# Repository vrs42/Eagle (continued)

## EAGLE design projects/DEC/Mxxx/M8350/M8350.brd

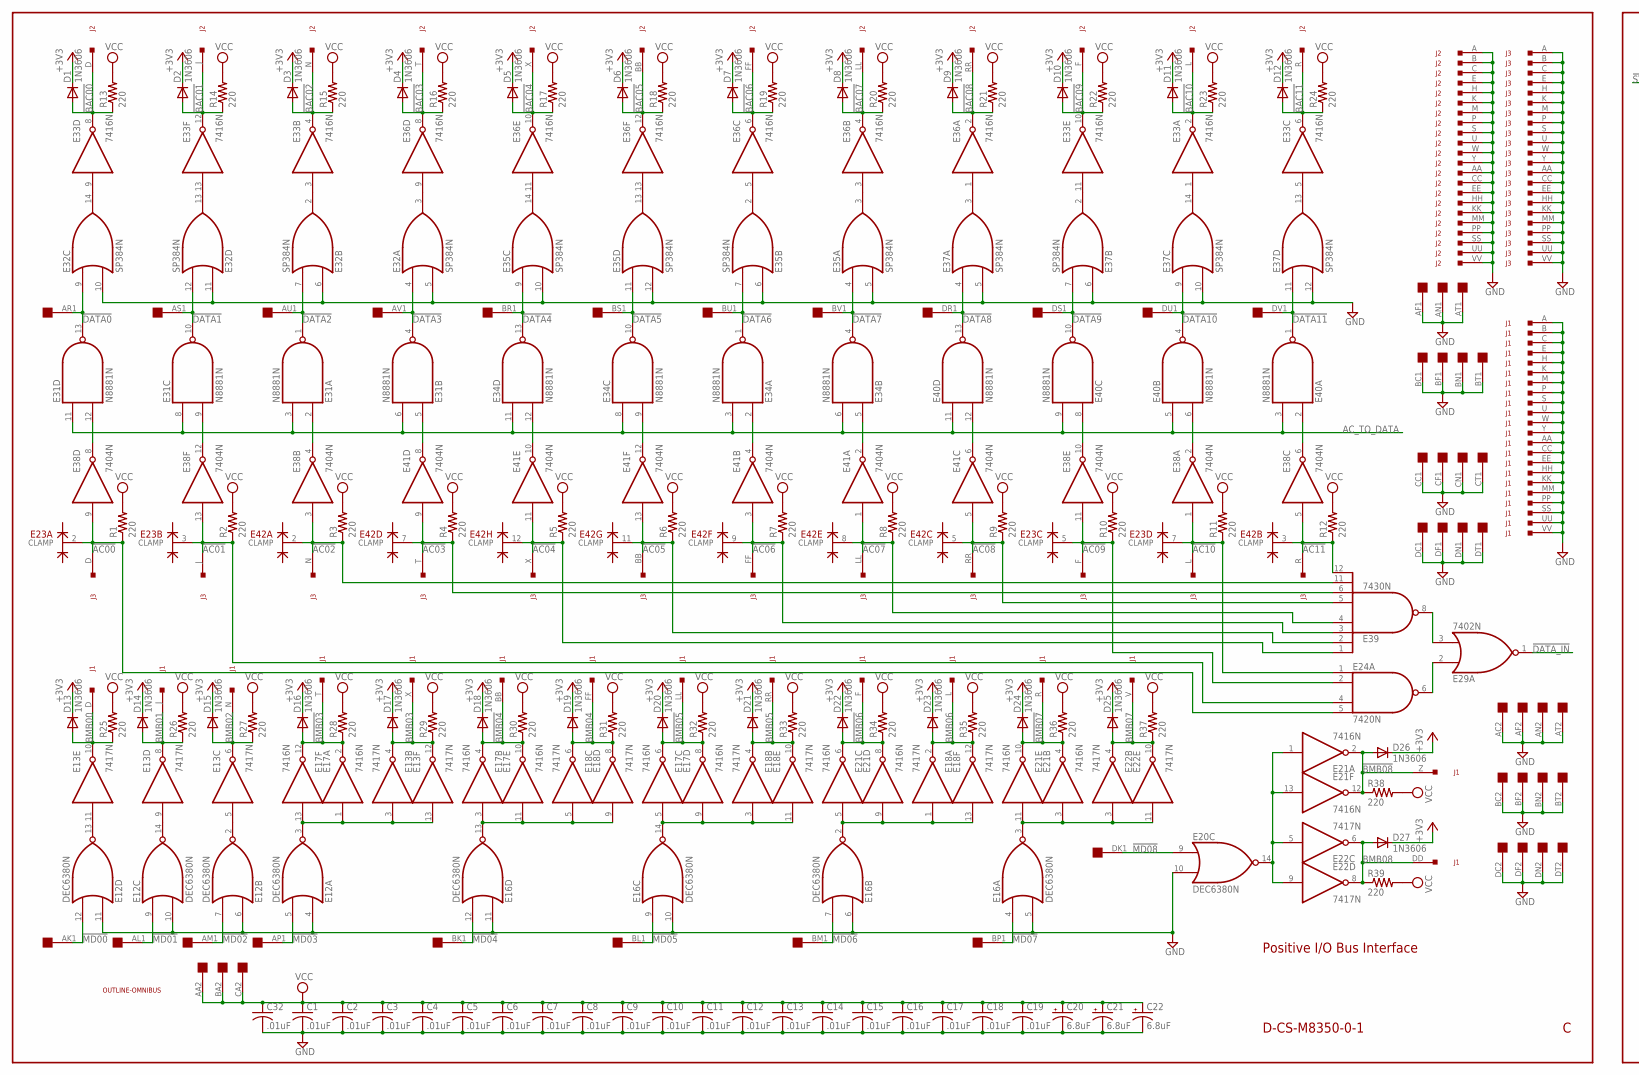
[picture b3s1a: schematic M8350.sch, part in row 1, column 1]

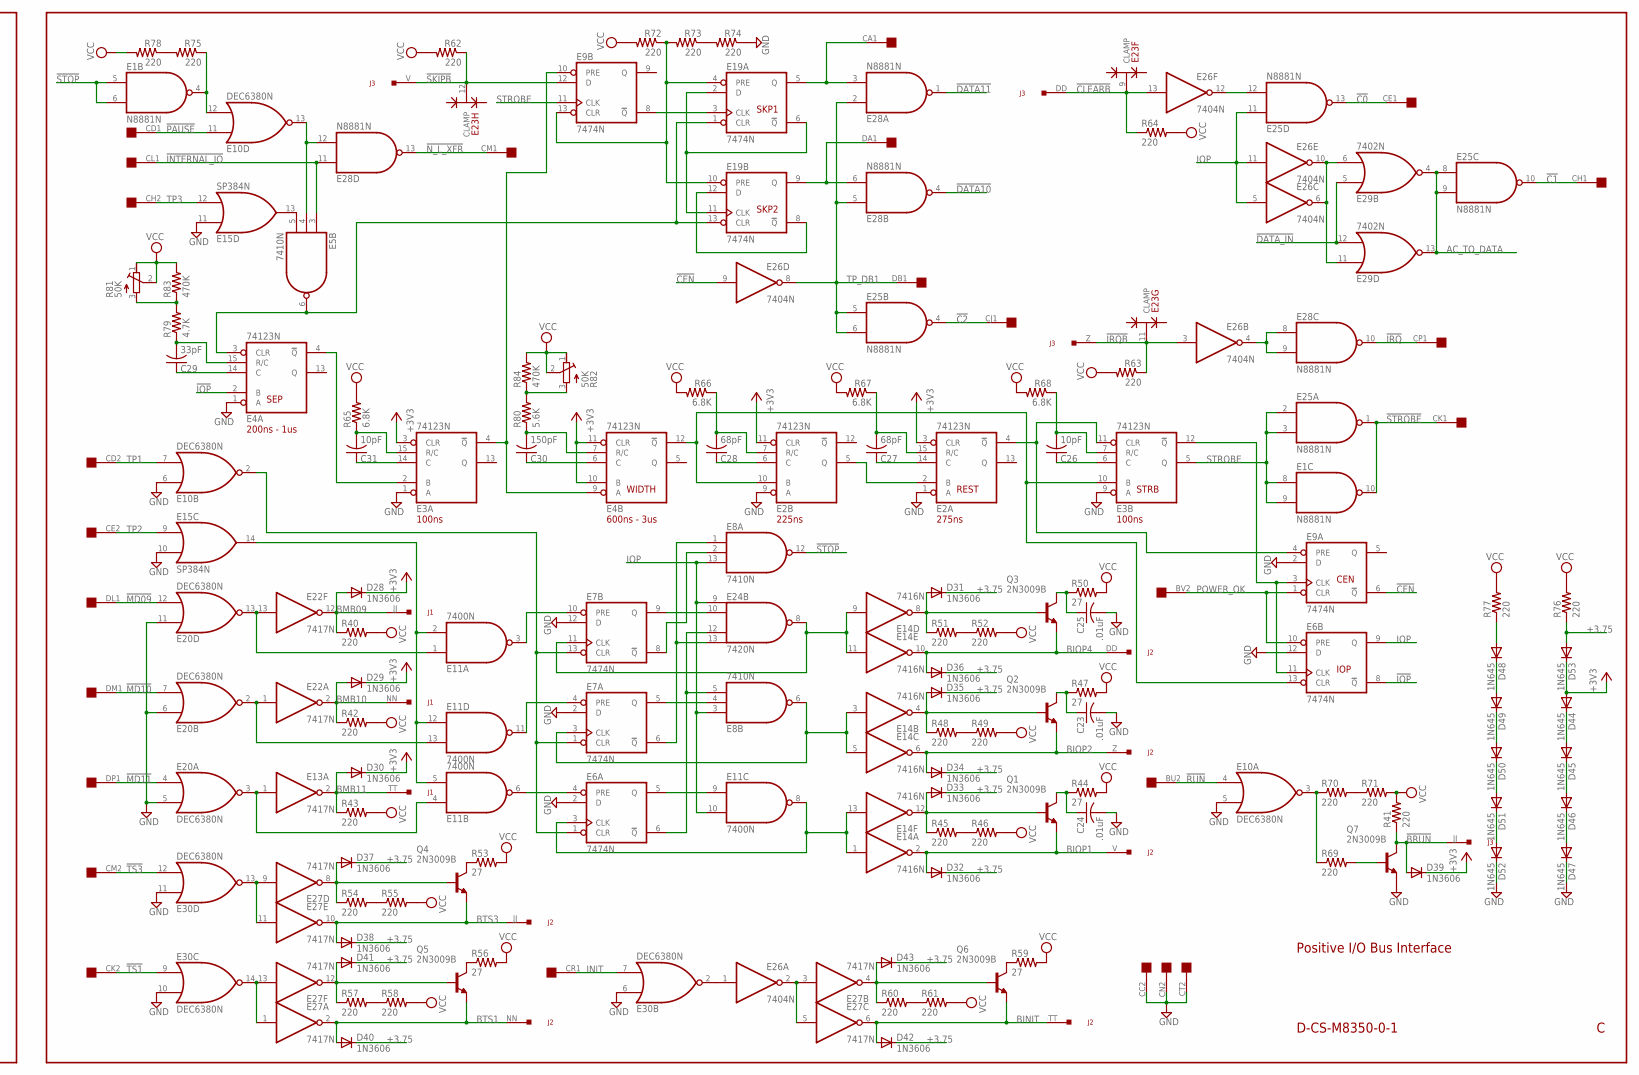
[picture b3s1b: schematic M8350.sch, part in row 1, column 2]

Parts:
C1, C2, C3, C4, C5, C6, C7, C8, C9, C10, C11, C12, C13, C14, C15, C16, C17, C18, C19, C23, C24, C25, C32: .01uF; C050-025X075
C20, C21, C22: 6.8uF; E12-8
C26, C31: 10pF; C050-025X075
C27, C28: 68pF; C050-025X075
C29: 33pF; C050-025X075
C30: 150pF; C050-025X075
D1, D2, D3, D4, D5, D6, D7, D8, D9, D10, D11, D12, D13, D14, D15, D16, D17, D18, D19, D20, D21, D22, D23, D24, D25, D26, D27, D28, D29, D30, D31, D32, D33, D34, D35, D36, D37, D38, D39, D40, D41, D42, D43: 1N3606; DO35-10
D44, D45, D46, D47, D48, D49, D50, D51, D52, D53: 1N645; DO35-10
E1, E25, E28, E31, E34, E40: N8881N; DIL14
E2, E3, E4: 74123N; DIL16
E5, E8: 7410N; DIL14
E6, E7, E9, E19: 7474N; DIL14
E10, E12, E16, E20, E30: DEC6380N; DIL14
E11: 7400N; DIL14
E13, E18, E22, E27: 7417N; DIL14
E14, E17, E21, E33, E36: 7416N; DIL14
E15, E32, E35, E37: SP384N; DIL14
E23, E42: DEC2501; DIL14
E24: 7420N; DIL14
E26, E38, E41: 7404N; DIL14
E29: 7402N; DIL14
E39: 7430N; DIL14
J1, J2, J3: DEC40PINSH; DEC40PINH
Q1, Q2, Q3, Q4, Q5, Q6, Q7: 2N3009B; TO5
R1, R2, R3, R4, R5, R6, R7, R8, R9, R10, R11, R12, R13, R14, R15, R16, R17, R18, R19, R20, R21, R22, R23, R24, R25, R26, R27, R28, R29, R30, R31, R32, R33, R34, R35, R36, R37, R38, R39, R40, R41, R42, R43, R45, R46, R48, R49, R51, R52, R54, R55, R57, R58, R60, R61, R62, R63, R64, R69, R70, R71, R72, R73, R74, R75, R76, R77, R78: 220; 0207/10
R44, R47, R50, R53, R56, R59: 27; 0207/10
R65, R66, R67, R68: 6.8K; 0207/10
R79: 4.7K; 0207/10
R80: 5.6K; 0207/10
R81, R82: 50K; 3006Y
R83, R84: 470K; 0207/10
U$1: OUTLINE-OMNIBUS; OMNIBUS
U$2: QUAD; EDGE-CON8

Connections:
!AC00: E23.2 (CLAMP), E24.5 (I3), E38.9 (I), J3.D, R1.1
!AC01: E23.3 (CLAMP), E24.4 (I2), E38.13 (I), J3.J, R2.1
!AC02: E38.3 (I), E39.11 (I6), E42.2 (CLAMP), J3.N, R3.1
!AC03: E39.6 (I5), E41.9 (I), E42.7 (CLAMP), J3.T, R4.1
!AC04: E39.1 (I0), E41.11 (I), E42.12 (CLAMP), J3.X, R5.1
!AC05: E39.2 (I1), E41.13 (I), E42.11 (CLAMP), J3.BB, R6.1
!AC06: E39.3 (I2), E41.3 (I), E42.9 (CLAMP), J3.FF, R7.1
!AC07: E39.4 (I3), E41.1 (I), E42.8 (CLAMP), J3.LL, R8.1
!AC08: E39.5 (I4), E41.5 (I), E42.5 (CLAMP), J3.RR, R9.1
!AC09: E23.5 (CLAMP), E24.2 (I1), E38.11 (I), J3.F, R10.1
!AC10: E23.7 (CLAMP), E24.1 (I0), E38.1 (I), J3.L, R11.1
!AC11: E38.5 (I), E39.12 (I7), E42.3 (CLAMP), J3.R, R12.1
!BAC00: D1.A, E33.8 (O), J2.D, R13.1
!BAC01: D2.A, E33.12 (O), J2.J, R14.1
!BAC02: D3.A, E33.4 (O), J2.N, R15.1
!BAC03: D4.A, E36.8 (O), J2.T, R16.1
!BAC04: D5.A, E36.10 (O), J2.X, R17.1
!BAC05: D6.A, E36.12 (O), J2.BB, R18.1
!BAC06: D7.A, E36.6 (O), J2.FF, R19.1
!BAC07: D8.A, E36.4 (O), J2.LL, R20.1
!BAC08: D9.A, E36.2 (O), J2.RR, R21.1
!BAC09: D10.A, E33.10 (O), J2.F, R22.1
!BAC10: D11.A, E33.2 (O), J2.L, R23.1
!BAC11: D12.A, E33.6 (O), J2.R, R24.1
!BMB03: D16.A, E17.2 (O), E17.12 (O), J1.T, R28.1
!BMB04: D18.A, E17.4 (O), E17.10 (O), J1.BB, R30.1
!BMB05: D20.A, E17.6 (O), E17.8 (O), J1.LL, R32.1
!BMB06: D22.A, E21.6 (O), E21.8 (O), J1.F, R34.1
!BMB07: D24.A, E21.4 (O), E21.10 (O), J1.R, R36.1
!BMB08: D26.A, E21.2 (O), E21.12 (O), J1.Z, R38.1
!BRUN: D39.A, J3.JJ, Q7.3 (C), R41.1
!C0: E25.13 (O), U$2.CE1
!C1: E25.10 (O), U$2.CH1
!C2: E25.4 (O), U$2.CJ1
!CEN: E9.6 (!Q), E26.9 (I)
!CLEARB: E23.9 (CLAMP), E26.13 (I), J3.DD, R64.1
!DATA0: E31.13 (O), E32.9 (I0), U$2.AR1
!DATA1: E31.10 (O), E32.12 (I1), U$2.AS1
!DATA2: E31.1 (O), E32.7 (I1), U$2.AU1
!DATA3: E31.4 (O), E32.4 (I0), U$2.AV1
!DATA4: E34.13 (O), E35.9 (I0), U$2.BR1
!DATA5: E34.10 (O), E35.11 (I0), U$2.BS1
!DATA6: E34.1 (O), E35.7 (I1), U$2.BU1
!DATA7: E34.4 (O), E35.4 (I0), U$2.BV1
!DATA8: E37.4 (I0), E40.13 (O), U$2.DR1
!DATA9: E37.7 (I1), E40.10 (O), U$2.DS1
!DATA10: E28.4 (O), E37.9 (I0), E40.4 (O), U$2.DU1
!DATA11: E28.1 (O), E37.11 (I0), E40.1 (O), U$2.DV1
!DATA_IN: E29.1 (O), E29.5 (I0), E29.12 (I1)
!INTERNAL_IO: E5.3 (I0), E28.11 (I0), U$2.CL1
!IOP: E4.2 (B), E6.8 (!Q)
!IRQ: E28.10 (O), U$2.CP1
!IRQB: E23.11 (CLAMP), E26.3 (I), J3.Z, R63.1
!MD00: E12.12 (I1), U$2.AK1
!MD01: E12.9 (I0), U$2.AL1
!MD02: E12.7 (I1), U$2.AM1
!MD03: E12.5 (I1), U$2.AP1
!MD04: E16.12 (I1), U$2.BK1
!MD05: E16.9 (I0), U$2.BL1
!MD06: E16.7 (I1), U$2.BM1
!MD07: E16.4 (I0), U$2.BP1
!MD08: E20.9 (I0), U$2.DK1
!MD09: E20.12 (I1), U$2.DL1
!MD10: E20.7 (I1), U$2.DM1
!MD11: E20.4 (I0), U$2.DP1
!N_L_XFR: E28.13 (O), U$2.CM1
!PAUSE: E10.11 (I0), U$2.CD1
!RUN: E10.4 (I0), U$2.BU2
!SKIPB: E9.12 (D), E23.12 (CLAMP), J3.V, R62.1
!STOP: E1.5 (I0), E1.6 (I1), E8.12 (O)
!STROBE: E1.10 (O), E25.1 (O), U$2.CK1
!TS1: E30.9 (I0), U$2.CK2
!TS3: E30.12 (I1), U$2.CM2
+3.75: D31.C, D32.C, D33.C, D34.C, D35.C, D36.C, D37.C, D38.C, D40.C, D41.C, D42.C, D43.C, D53.A, R76.1
+3V3: D1.C, D2.C, D3.C, D4.C, D5.C, D6.C, D7.C, D8.C, D9.C, D10.C, D11.C, D12.C, D13.C, D14.C, D15.C, D16.C, D17.C, D18.C, D19.C, D20.C, D21.C, D22.C, D23.C, D24.C, D25.C, D26.C, D27.C, D28.C, D29.C, D30.C, D39.C, D44.A, D53.C, E2.3 (CLR), E2.11 (CLR), E3.3 (CLR), E4.10 (B), E4.11 (CLR)
AC_TO_DATA: E25.8 (I0), E25.9 (I1), E29.4 (O), E29.13 (O), E31.3 (I1), E31.6 (I1), E31.8 (I0), E31.11 (I0), E34.3 (I1), E34.6 (I1), E34.8 (I0), E34.11 (I0), E40.3 (I1), E40.5 (I0), E40.9 (I1), E40.11 (I0)
BINIT: D42.A, E27.6 (O), J2.TT, Q6.1 (E)
BIOP1: D32.A, E14.2 (O), J2.V, Q1.1 (E)
BIOP2: D34.A, E14.6 (O), J2.Z, Q2.1 (E)
BIOP4: D36.A, E14.10 (O), J2.DD, Q3.1 (E)
BMB00: D13.A, E13.10 (O), J1.D, R25.1
BMB01: D14.A, E13.8 (O), J1.J, R26.1
BMB02: D15.A, E13.6 (O), J1.N, R27.1
BMB03: D17.A, E13.4 (O), E13.12 (O), J1.X, R29.1
BMB04: D19.A, E18.6 (O), E18.8 (O), J1.FF, R31.1
BMB05: D21.A, E18.4 (O), E18.10 (O), J1.RR, R33.1
BMB06: D23.A, E18.2 (O), E18.12 (O), J1.L, R35.1
BMB07: D25.A, E22.4 (O), E22.10 (O), J1.V, R37.1
BMB08: D27.A, E22.6 (O), E22.8 (O), J1.DD, R39.1
BMB09: D28.A, E22.12 (O), J1.JJ, R40.1
BMB10: D29.A, E22.2 (O), J1.NN, R42.1
BMB11: D30.A, E13.2 (O), J1.TT, R43.1
BTS1: D40.A, E27.2 (O), J2.NN, Q5.1 (E)
BTS3: D38.A, E27.10 (O), J2.JJ, Q4.1 (E)
GND: C1.2, C2.2, C3.2, C4.2, C5.2, C6.2, C7.2, C8.2, C9.2, C10.2, C11.2, C12.2, C13.2, C14.2, C15.2, C16.2, C17.2, C18.2, C19.2, C20.-, C21.-, C22.-, C23.2, C24.2, C25.2, C32.2, D47.C, D52.C, E1.7 (GND), E2.1 (A), E2.8 (GND), E2.9 (A), E3.1 (A), E3.8 (GND), E3.9 (A), E4.1 (A), E4.8 (GND), E5.7 (GND), E6.2 (D), E6.7 (GND), E6.12 (D), E7.2 (D), E7.7 (GND), E7.12 (D), E8.7 (GND), E9.2 (D), E9.7 (GND), E10.1 (GND), E10.5 (I1), E10.6 (I0), E11.7 (GND), E12.1 (GND), E12.4 (I0), E12.6 (I0), E12.10 (I1), E12.11 (I0), E13.7 (GND), E14.7 (GND), E15.1 (GND), E15.10 (I1), E15.11 (I0), E16.1 (GND), E16.5 (I1), E16.6 (I0), E16.10 (I1), E16.11 (I0), E17.7 (GND), E18.7 (GND), E19.7 (GND), E20.1 (GND), E20.5 (I1), E20.6 (I0), E20.10 (I1), E20.11 (I0), E21.7 (GND), E22.7 (GND), E23.14 (GND), E24.7 (GND), E25.7 (GND), E26.7 (GND), E27.7 (GND), E28.7 (GND), E29.7 (GND), E30.1 (GND), E30.6 (I0), E30.10 (I1), E30.11 (I0), E31.7 (GND), E32.1 (GND), E32.5 (I1), E32.6 (I0), E32.10 (I1), E32.11 (I0), E33.7 (GND), E34.7 (GND), E35.1 (GND), E35.5 (I1), E35.6 (I0), E35.10 (I1), E35.12 (I1), E36.7 (GND), E37.1 (GND), E37.5 (I1), E37.6 (I0), E37.10 (I1), E37.12 (I1), E38.7 (GND), E39.7 (GND), E40.7 (GND), E41.7 (GND), E42.14 (GND), J1.A, J1.AA, J1.B, J1.C, J1.CC, J1.E, J1.EE, J1.H, J1.HH, J1.K, J1.KK, J1.M, J1.MM, J1.P, J1.PP, J1.S, J1.SS, J1.U, J1.UU, J1.VV, J1.W, J1.Y, J2.A, J2.AA, J2.B, J2.C, J2.CC, J2.E, J2.EE, J2.H, J2.HH, J2.K, J2.KK, J2.M, J2.MM, J2.P, J2.PP, J2.S, J2.SS, J2.U, J2.UU, J2.VV, J2.W, J2.Y, J3.A, J3.AA, J3.B, J3.C, J3.CC, J3.E, J3.EE, J3.H, J3.HH, J3.K, J3.KK, J3.M, J3.MM, J3.P, J3.PP, J3.S, J3.SS, J3.U, J3.UU, J3.VV, J3.W, J3.Y, Q7.1 (E), R74.1, U$2.AC2, U$2.AF1, U$2.AF2, U$2.AN1, U$2.AN2, U$2.AT1, U$2.AT2, U$2.BC1, U$2.BC2, U$2.BF1, U$2.BF2, U$2.BN1, U$2.BN2, U$2.BT1, U$2.BT2, U$2.CC1, U$2.CC2, U$2.CF1, U$2.CN1, U$2.CN2, U$2.CT1, U$2.CT2, U$2.DC1, U$2.DC2, U$2.DF1, U$2.DF2, U$2.DN1, U$2.DN2, U$2.DT1, U$2.DT2
INIT: E30.7 (I1), U$2.CR1
IOP: E6.9 (Q), E8.3 (I0), E8.13 (I2), E11.10 (I1), E24.9 (I0), E25.11 (I0), E26.5 (I), E26.11 (I)
unnamed: E32.14 (O), E33.9 (I)
unnamed: E31.2 (I0), E38.4 (O)
unnamed: E34.12 (I1), E41.10 (O)
unnamed: E31.12 (I1), E38.8 (O)
unnamed: E31.9 (I1), E38.12 (O)
unnamed: E16.13 (O), E17.3 (I), E17.11 (I), E18.5 (I), E18.9 (I)
unnamed: E34.9 (I1), E41.12 (O)
unnamed: E34.2 (I0), E41.4 (O)
unnamed: E34.5 (I0), E41.2 (O)
unnamed: E40.12 (I1), E41.6 (O)
unnamed: E38.6 (O), E40.2 (I0)
unnamed: E38.10 (O), E40.8 (I0)
unnamed: E38.2 (O), E40.6 (I1)
unnamed: E24.6 (O), E29.2 (I0)
unnamed: E29.3 (I1), E39.8 (O)
unnamed: E32.2 (O), E33.3 (I)
unnamed: E32.13 (O), E33.13 (I)
unnamed: E31.5 (I0), E41.8 (O)
unnamed: E32.3 (O), E36.9 (I)
unnamed: E35.14 (O), E36.11 (I)
unnamed: E35.13 (O), E36.13 (I)
unnamed: E35.2 (O), E36.5 (I)
unnamed: E35.3 (O), E36.3 (I)
unnamed: E36.1 (I), E37.3 (O)
unnamed: E33.11 (I), E37.2 (O)
unnamed: E33.1 (I), E37.14 (O)
unnamed: E33.5 (I), E37.13 (O)
unnamed: E12.13 (O), E13.11 (I)
unnamed: E16.14 (O), E17.5 (I), E17.9 (I), E18.3 (I), E18.11 (I)
unnamed: E16.3 (O), E21.3 (I), E21.11 (I), E22.3 (I), E22.11 (I)
unnamed: E20.14 (O), E21.1 (I), E21.13 (I), E22.5 (I), E22.9 (I)
unnamed: E12.14 (O), E13.9 (I)
unnamed: E16.2 (O), E18.1 (I), E18.13 (I), E21.5 (I), E21.9 (I)
unnamed: E11.4 (I0), E13.1 (I), E20.3 (O)
unnamed: E11.1 (I0), E20.13 (O), E22.13 (I)
unnamed: E12.2 (O), E13.5 (I)
unnamed: E12.3 (O), E13.3 (I), E13.13 (I), E17.1 (I), E17.13 (I)
unnamed: E11.13 (I1), E20.2 (O), E22.1 (I)
unnamed: R54.2, R55.1
unnamed: E3.2 (B), E4.4 (!Q)
unnamed: E27.9 (I), E27.11 (I), E30.13 (O)
unnamed: D37.A, E27.8 (O), Q4.2 (B), R54.1
unnamed: Q4.3 (C), R53.1
unnamed: E3.4 (!Q), E4.9 (A), E9.10 (PRE)
unnamed: D41.A, E27.12 (O), Q5.2 (B), R57.1
unnamed: E2.10 (B), E3.10 (B), E4.12 (!Q), E6.13 (CLR)
unnamed: E27.1 (I), E27.13 (I), E30.14 (O)
unnamed: R57.2, R58.1
unnamed: E2.2 (B), E2.5 (Q)
unnamed: Q5.3 (C), R56.1
unnamed: E2.4 (!Q), E3.11 (CLR), E9.4 (PRE)
unnamed: E26.1 (I), E30.2 (O)
unnamed: E26.2 (O), E27.3 (I), E27.5 (I)
unnamed: R60.2, R61.1
unnamed: D43.A, E27.4 (O), Q6.2 (B), R60.1
unnamed: Q6.3 (C), R59.1
unnamed: R80.2, R82.3 (E), R84.1
unnamed: C29.2, E4.15 (R/C), R79.1
unnamed: C29.1, E4.14 (C)
unnamed: E11.2 (I1), E11.5 (I1), E11.12 (I0), E15.14 (O)
unnamed: R79.2, R81.3 (E), R83.1
unnamed: C31.1, E3.14 (C)
unnamed: C31.2, E3.15 (R/C), R65.1
unnamed: C30.1, E4.6 (C)
unnamed: C30.2, E4.7 (R/C), R80.1
unnamed: C28.1, E2.6 (C)
unnamed: C28.2, E2.7 (R/C), R66.1
unnamed: C27.1, E2.14 (C)
unnamed: C27.2, E2.15 (R/C), R67.1
unnamed: C26.1, E3.6 (C)
unnamed: C26.2, E3.7 (R/C), R68.1
unnamed: E7.10 (PRE), E11.3 (O)
unnamed: E7.4 (PRE), E11.11 (O)
unnamed: E6.4 (PRE), E11.6 (O)
unnamed: E6.1 (CLR), E7.1 (CLR), E7.13 (CLR), E10.2 (O)
unnamed: E6.5 (Q), E11.9 (I0)
unnamed: E7.5 (Q), E8.4 (I1)
unnamed: E7.9 (Q), E24.10 (I1)
unnamed: E6.6 (!Q), E8.5 (I2), E24.12 (I2)
unnamed: E7.6 (!Q), E8.1 (I0), E24.13 (I3)
unnamed: E7.8 (!Q), E8.2 (I1)
unnamed: E7.3 (CLK), E8.6 (O), E14.3 (I), E14.5 (I)
unnamed: E6.3 (CLK), E11.8 (O), E14.1 (I), E14.13 (I)
unnamed: E7.11 (CLK), E14.9 (I), E14.11 (I), E24.8 (O)
unnamed: D48.A, R77.1
unnamed: D44.C, D45.A
unnamed: D45.C, D46.A
unnamed: D46.C, D47.A
unnamed: D48.C, D49.A
unnamed: D51.C, D52.A
unnamed: D50.C, D51.A
unnamed: D49.C, D50.A
unnamed: D35.A, E14.4 (O), Q2.2 (B), R48.1
unnamed: D33.A, E14.12 (O), Q1.2 (B), R45.1
unnamed: R48.2, R49.1
unnamed: R51.2, R52.1
unnamed: D31.A, E14.8 (O), Q3.2 (B), R51.1
unnamed: C25.1, Q3.3 (C), R50.1
unnamed: E10.3 (O), R69.1, R70.1
unnamed: R70.2, R71.1
unnamed: C23.1, Q2.3 (C), R47.1
unnamed: Q7.2 (B), R69.2
unnamed: C24.1, Q1.3 (C), R44.1
unnamed: R45.2, R46.1
unnamed: R73.1, R74.2
unnamed: E9.13 (CLR), E19.4 (PRE), E19.10 (PRE), R72.1, R73.2
unnamed: R75.2, R78.1
unnamed: E26.6 (O), E26.10 (O), E29.6 (I1), E29.11 (I0)
unnamed: E25.12 (I1), E26.12 (O)
unnamed: E26.4 (O), E28.8 (I0), E28.9 (I1)
unnamed: E5.5 (I2), E15.13 (O)
unnamed: E5.4 (I1), E10.13 (O), E28.12 (I1)
unnamed: E4.3 (CLR), E5.6 (O), E19.1 (CLR), E19.13 (CLR)
unnamed: E19.2 (D), E19.6 (!Q), E19.11 (CLK)
unnamed: E1.4 (O), E10.12 (I1), R75.1
unnamed: E9.8 (!Q), E19.3 (CLK)
unnamed: E19.8 (!Q), E19.12 (D)
unnamed: E3.12 (!Q), E6.11 (CLK), E9.3 (CLK)
POWER_OK: E6.10 (PRE), E9.1 (CLR), U$2.BV2
SKP1: E19.5 (Q), E28.3 (I1), U$2.CA1
SKP2: E19.9 (Q), E28.6 (I1), U$2.DA1
STROBE: E1.8 (I0), E1.9 (I1), E3.5 (Q), E9.11 (CLK), E25.2 (I0), E25.3 (I1)
TP1: E10.7 (I1), U$2.CD2
TP2: E15.9 (I0), U$2.CE2
TP3: E15.12 (I1), U$2.CH2
TP_DB1: E25.5 (I0), E25.6 (I1), E26.8 (O), E28.2 (I0), E28.5 (I0), U$2.DB1
VCC: C1.1, C2.1, C3.1, C4.1, C5.1, C6.1, C7.1, C8.1, C9.1, C10.1, C11.1, C12.1, C13.1, C14.1, C15.1, C16.1, C17.1, C18.1, C19.1, C20.+, C21.+, C22.+, C32.1, E1.14 (VCC), E2.16 (VCC), E3.16 (VCC), E4.16 (VCC), E5.14 (VCC), E6.14 (VCC), E7.14 (VCC), E8.14 (VCC), E9.14 (VCC), E10.8 (VCC), E11.14 (VCC), E12.8 (VCC), E13.14 (VCC), E14.14 (VCC), E15.8 (VCC), E16.8 (VCC), E17.14 (VCC), E18.14 (VCC), E19.14 (VCC), E20.8 (VCC), E21.14 (VCC), E22.14 (VCC), E23.1 (VCC), E24.14 (VCC), E25.14 (VCC), E26.14 (VCC), E27.14 (VCC), E28.14 (VCC), E29.14 (VCC), E30.8 (VCC), E31.14 (VCC), E32.8 (VCC), E33.14 (VCC), E34.14 (VCC), E35.8 (VCC), E36.14 (VCC), E37.8 (VCC), E38.14 (VCC), E39.14 (VCC), E40.14 (VCC), E41.14 (VCC), E42.1 (VCC), R1.2, R2.2, R3.2, R4.2, R5.2, R6.2, R7.2, R8.2, R9.2, R10.2, R11.2, R12.2, R13.2, R14.2, R15.2, R16.2, R17.2, R18.2, R19.2, R20.2, R21.2, R22.2, R23.2, R24.2, R25.2, R26.2, R27.2, R28.2, R29.2, R30.2, R31.2, R32.2, R33.2, R34.2, R35.2, R36.2, R37.2, R38.2, R39.2, R40.2, R41.2, R42.2, R43.2, R44.2, R46.2, R47.2, R49.2, R50.2, R52.2, R53.2, R55.2, R56.2, R58.2, R59.2, R61.2, R62.2, R63.2, R64.2, R65.2, R66.2, R67.2, R68.2, R71.2, R72.2, R76.2, R77.2, R78.2, R81.1 (A), R81.2 (S), R82.1 (A), R82.2 (S), R83.2, R84.2, U$2.AA2, U$2.BA2, U$2.CA2

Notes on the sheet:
D-CS-M8350-0-1
Positive I/O Bus Interface
SEP
200ns - 1us
100ns
600ns - 3us
225ns
275ns
WIDTH
REST
STRB
CEN
IOP
SKP1
SKP2

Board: 2 copper layers, 223 parts (0 on the bottom side), 224 nets, no tracks yet.

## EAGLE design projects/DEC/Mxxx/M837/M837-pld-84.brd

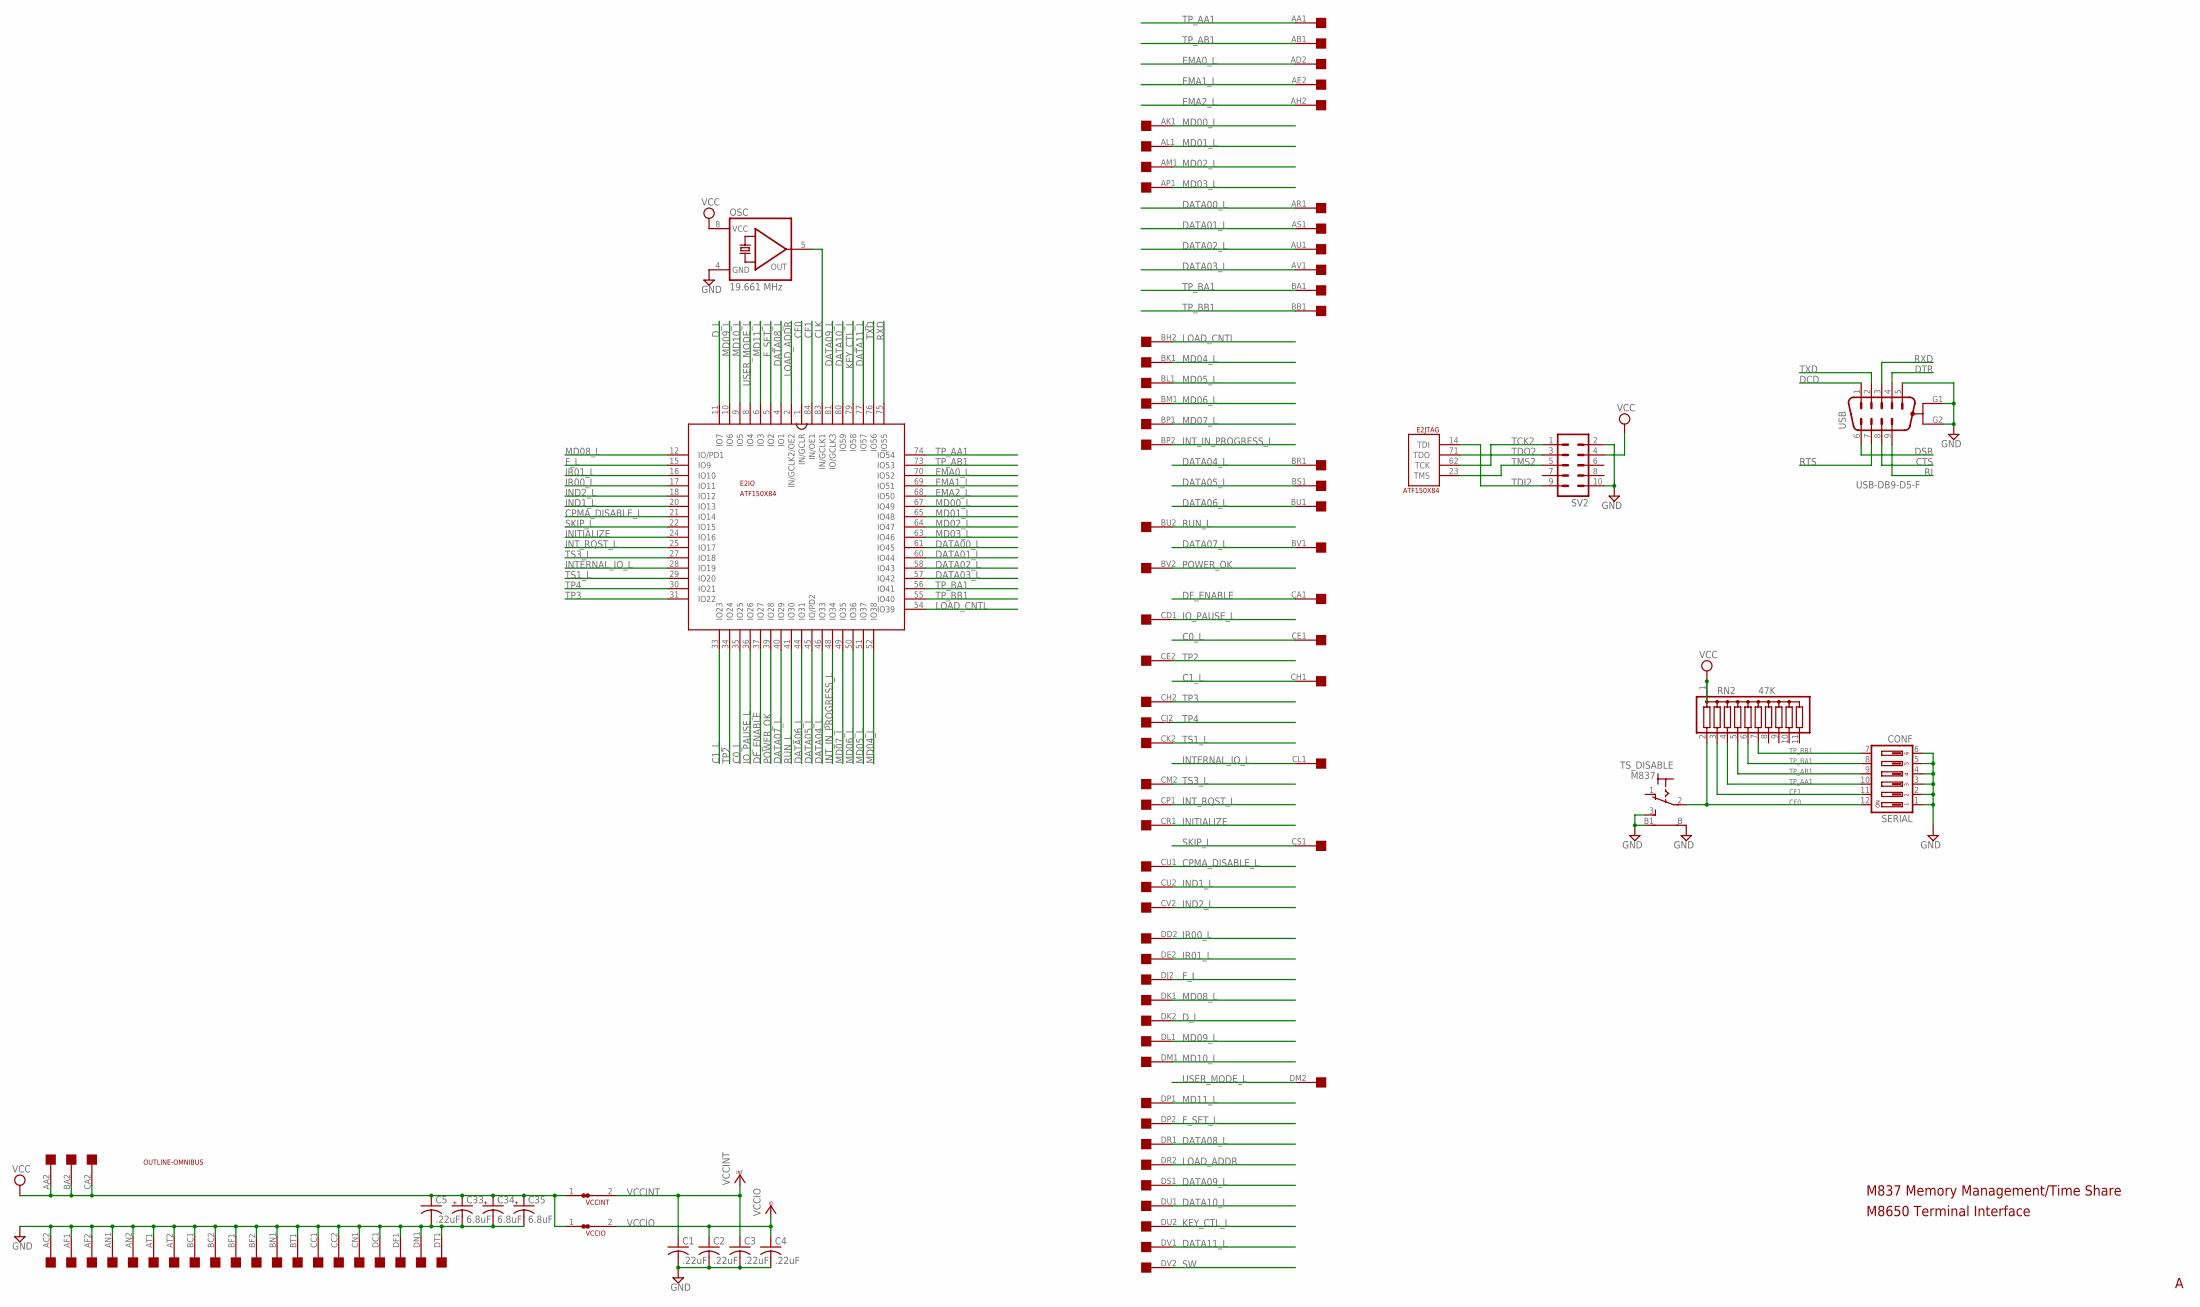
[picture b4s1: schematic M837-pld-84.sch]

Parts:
C1, C2, C3, C4, C5: .22uF; C063-025X075
C33, C34, C35: 6.8uF; E12-8
E2: ATF150X84; S84
OSC: 19.661 MHz; DIL08S
RN2: 47K; SIL11
SERIAL: CONF; DP-06
SV2: ML10
TS_DISABLE: M837; 9070-1W
U$1: QUAD; EDGE-CON8
U$2: OUTLINE-OMNIBUS; OMNIBUS
USB: USB-DB9-D5-F; AMP_DB-9RA
VCCINT: JUMPER-NC1; NC1
VCCIO: JUMPER-NC1; NC1

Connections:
C0_L: E2.35 (IO25), U$1.CE1
C1_L: E2.33 (IO23), U$1.CH1
CF0: E2.1 (IN/GCLR), RN2.2, SERIAL.12, TS_DISABLE.2
CF1: E2.84 (IN/OE1), RN2.3, SERIAL.11
CLK: E2.83 (IN/GCLK1), OSC.5 (OUT)
CPMA_DISABLE_L: E2.21 (IO14), U$1.CU1
CTS: USB.8
DATA00_L: E2.61 (IO45), U$1.AR1
DATA01_L: E2.60 (IO44), U$1.AS1
DATA02_L: E2.58 (IO43), U$1.AU1
DATA03_L: E2.57 (IO42), U$1.AV1
DATA04_L: E2.46 (IO33), U$1.BR1
DATA05_L: E2.45 (IO/PD2), U$1.BS1
DATA06_L: E2.44 (IO31), U$1.BU1
DATA07_L: E2.40 (IO29), U$1.BV1
DATA08_L: E2.4 (IO1), U$1.DR1
DATA09_L: E2.81 (IO/GCLK3), U$1.DS1
DATA10_L: E2.80 (IO59), U$1.DU1
DATA11_L: E2.77 (IO57), U$1.DV1
DCD: USB.1
DF_ENABLE: E2.37 (IO27), U$1.CA1
DSR: USB.6
DTR: USB.4
D_L: E2.11 (IO7), U$1.DK2
EMA0_L: E2.70 (IO52), U$1.AD2
EMA1_L: E2.69 (IO51), U$1.AE2
EMA2_L: E2.68 (IO50), U$1.AH2
F_L: E2.15 (IO9), U$1.DJ2
F_SET_L: E2.5 (IO2), U$1.DP2
GND: C1.2, C2.2, C3.2, C4.2, C5.2, C33.-, C34.-, C35.-, E2.7 (GND), E2.19 (GND), E2.32 (GND), E2.42 (GND), E2.47 (GND), E2.59 (GND), E2.72 (GND), E2.82 (GND), OSC.4 (GND), SERIAL.1, SERIAL.2, SERIAL.3, SERIAL.4, SERIAL.5, SERIAL.6, SV2.2, SV2.10, TS_DISABLE.3 (S), TS_DISABLE.B, TS_DISABLE.B1, U$1.AC2, U$1.AF1, U$1.AF2, U$1.AN1, U$1.AN2, U$1.AT1, U$1.AT2, U$1.BC1, U$1.BC2, U$1.BF1, U$1.BF2, U$1.BN1, U$1.BT1, U$1.CC1, U$1.CC2, U$1.CN1, U$1.DC1, U$1.DF1, U$1.DN1, U$1.DT1, USB.5, USB.G1, USB.G2
IND1_L: E2.20 (IO13), U$1.CU2
IND2_L: E2.18 (IO12), U$1.CV2
INITIALIZE: E2.24 (IO16), U$1.CR1
INTERNAL_IO_L: E2.28 (IO19), U$1.CL1
INT_IN_PROGRESS_L: E2.48 (IO34), U$1.BP2
INT_RQST_L: E2.25 (IO17), U$1.CP1
IO_PAUSE_L: E2.36 (IO26), U$1.CD1
IR00_L: E2.17 (IO11), U$1.DD2
IR01_L: E2.16 (IO10), U$1.DE2
KEY_CTL_L: E2.79 (IO58), U$1.DU2
LOAD_ADDR: E2.2 (IN/GCLK2/OE2), U$1.DR2
LOAD_CNTL: E2.54 (IO39), U$1.BH2
MD00_L: E2.67 (IO49), U$1.AK1
MD01_L: E2.65 (IO48), U$1.AL1
MD02_L: E2.64 (IO47), U$1.AM1
MD03_L: E2.63 (IO46), U$1.AP1
MD04_L: E2.52 (IO38), U$1.BK1
MD05_L: E2.51 (IO37), U$1.BL1
MD06_L: E2.50 (IO36), U$1.BM1
MD07_L: E2.49 (IO35), U$1.BP1
MD08_L: E2.12 (IO/PD1), U$1.DK1
MD09_L: E2.10 (IO6), U$1.DL1
MD10_L: E2.9 (IO5), U$1.DM1
MD11_L: E2.6 (IO3), U$1.DP1
POWER_OK: E2.39 (IO28), U$1.BV2
RI: USB.9
RTS: USB.7
RUN_L: E2.41 (IO30), U$1.BU2
RXD: E2.75 (IO55), USB.3
SKIP_L: E2.22 (IO15), U$1.CS1
SW: U$1.DV2
TCK2: E2.62 (TCK), SV2.1
TDI2: E2.14 (TDI), SV2.9
TDO2: E2.71 (TDO), SV2.3
TMS2: E2.23 (TMS), SV2.5
TP2: E2.34 (IO24), U$1.CE2
TP3: E2.31 (IO22), U$1.CH2
TP4: E2.30 (IO21), U$1.CJ2
TP_AA1: E2.74 (IO54), RN2.4, SERIAL.10, U$1.AA1
TP_AB1: E2.73 (IO53), RN2.5, SERIAL.9, U$1.AB1
TP_BA1: E2.56 (IO41), RN2.6, SERIAL.8, U$1.BA1
TP_BB1: E2.55 (IO40), RN2.7, SERIAL.7, U$1.BB1
TS1_L: E2.29 (IO20), U$1.CK2
TS3_L: E2.27 (IO18), U$1.CM2
TXD: E2.76 (IO56), USB.2
USER_MODE_L: E2.8 (IO4), U$1.DM2
VCC: C5.1, C33.+, C34.+, C35.+, OSC.8 (VCC), RN2.1, SV2.4, U$1.AA2, U$1.BA2, U$1.CA2, VCCINT.1, VCCIO.1
VCCINT: C1.1, C3.1, E2.3 (VCCINT), E2.43 (VCCINT), VCCINT.2
VCCIO: C2.1, C4.1, E2.13 (VCCIO), E2.26 (VCCIO), E2.38 (VCCIO), E2.53 (VCCIO), E2.66 (VCCIO), E2.78 (VCCIO), VCCIO.2

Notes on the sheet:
M837 Memory Management/Time Share
M8650 Terminal Interface

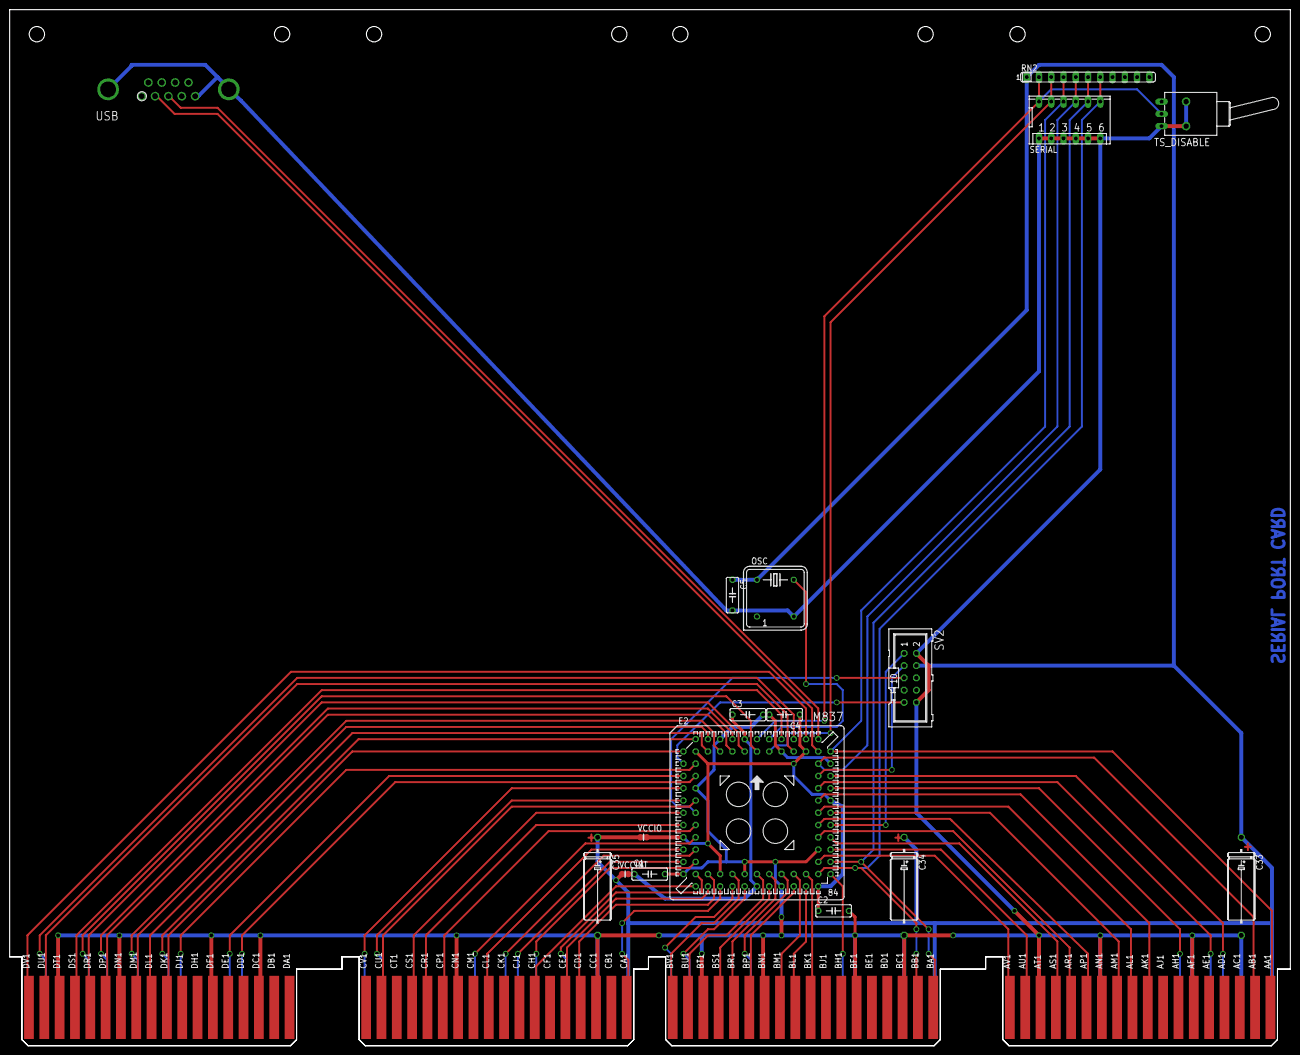
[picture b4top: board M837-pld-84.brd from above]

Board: 2 copper layers, 265.3 x 214.6 mm, 19 parts (0 on the bottom side), 72 nets.

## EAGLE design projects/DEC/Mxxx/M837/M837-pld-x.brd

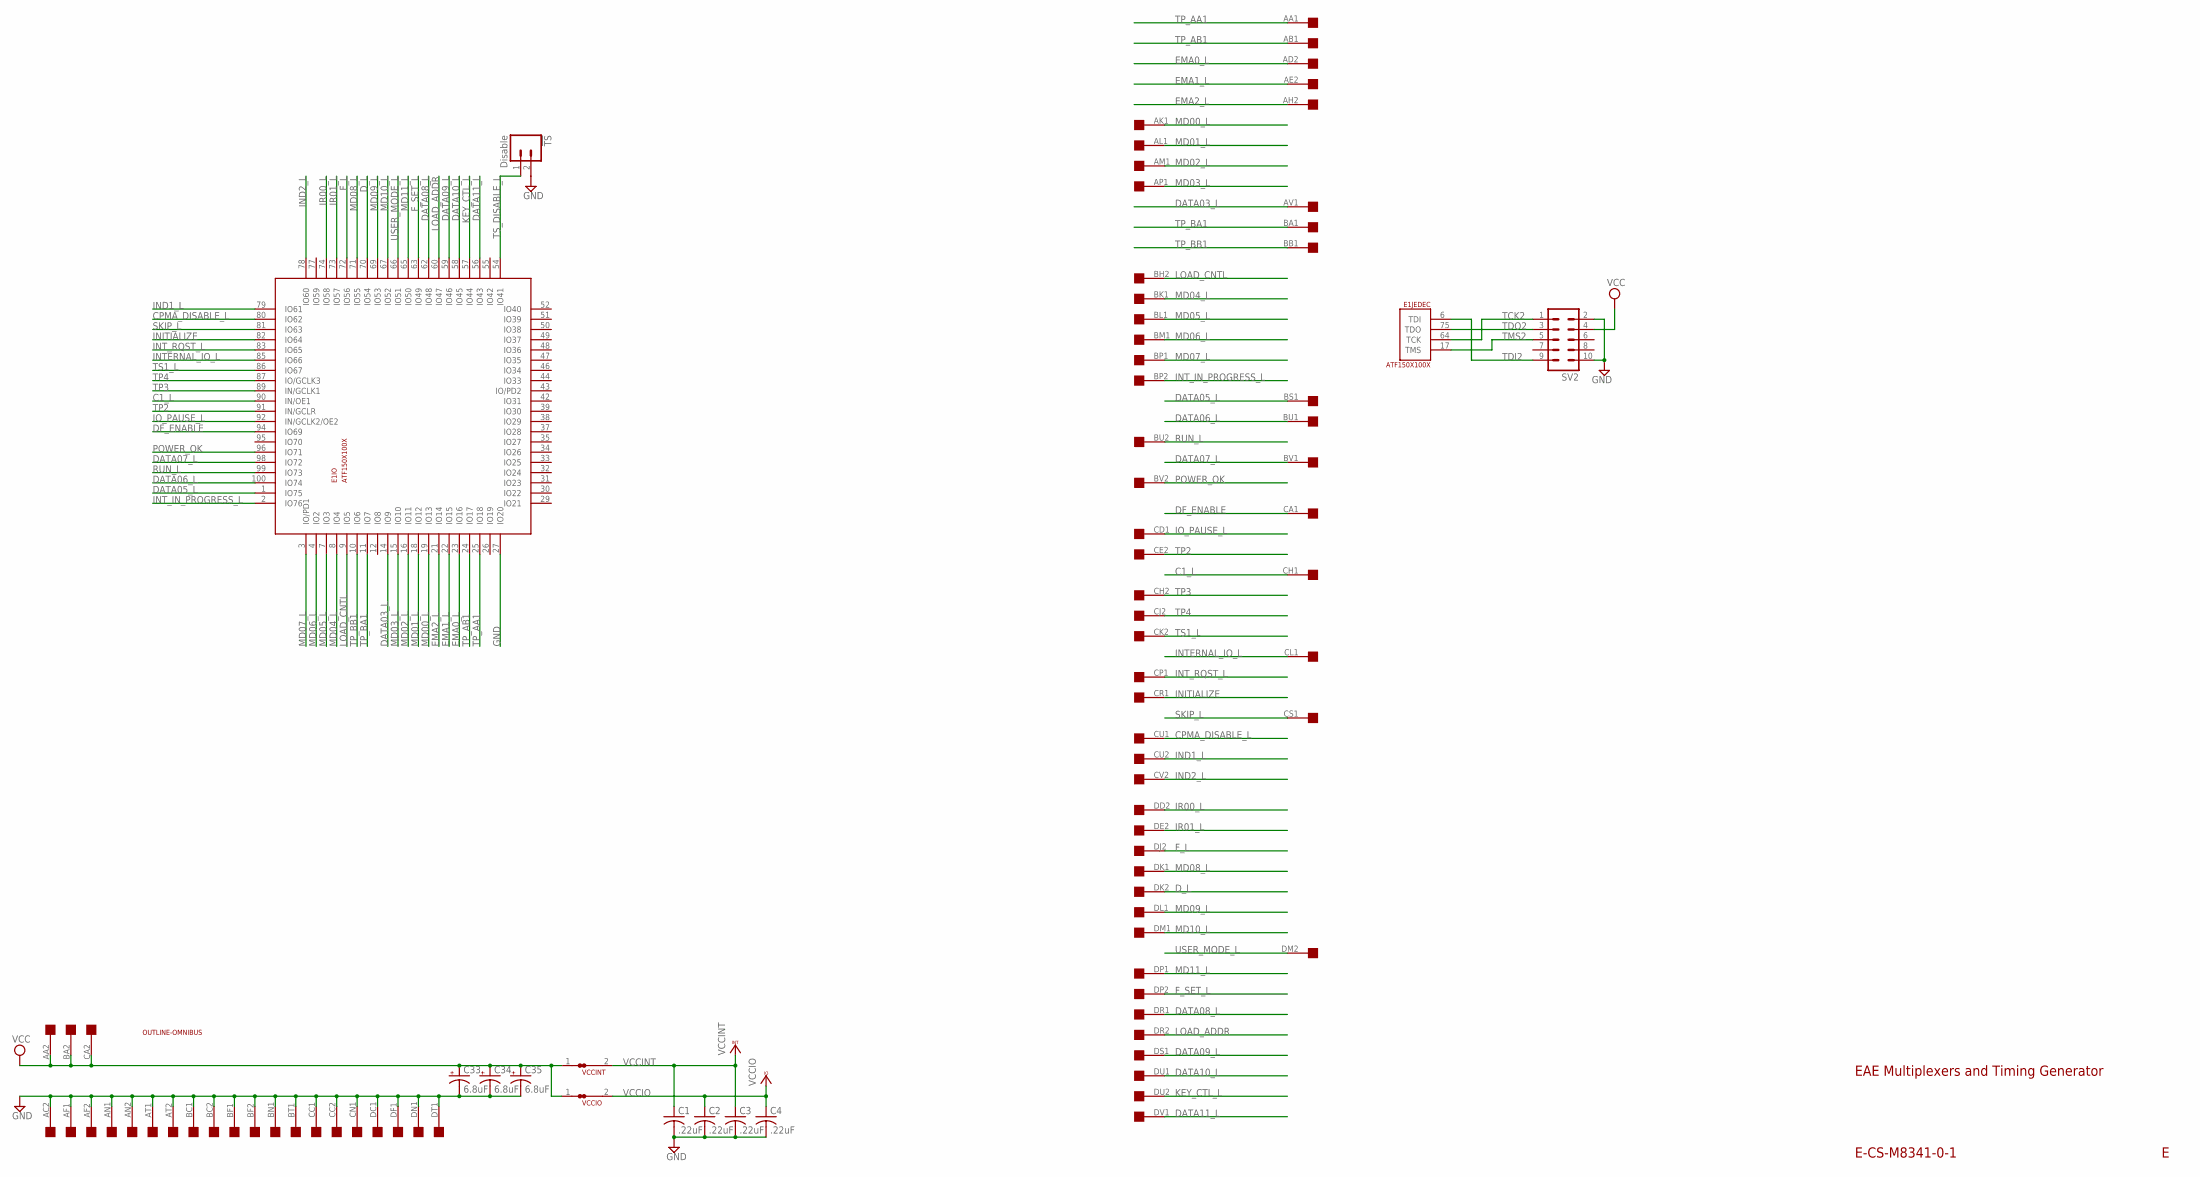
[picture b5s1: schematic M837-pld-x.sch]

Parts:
!TS: Disable; 02P
C1, C2, C3, C4: .22uF; C063-025X075
C33, C34, C35: 6.8uF; E12-8
E1: ATF150X100X; TH100B
SV2: ML10
U$1: QUAD; EDGE-CON8
U$2: OUTLINE-OMNIBUS; OMNIBUS
VCCINT: JUMPER-NC1; NC1
VCCIO: JUMPER-NC1; NC1

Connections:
C1_L: E1.90 (IN/OE1), U$1.CH1
CPMA_DISABLE_L: E1.80 (IO62), U$1.CU1
DATA03_L: E1.14 (IO9), U$1.AV1
DATA05_L: E1.1 (IO75), U$1.BS1
DATA06_L: E1.100 (IO74), U$1.BU1
DATA07_L: E1.98 (IO72), U$1.BV1
DATA08_L: E1.62 (IO48), U$1.DR1
DATA09_L: E1.59 (IO46), U$1.DS1
DATA10_L: E1.58 (IO45), U$1.DU1
DATA11_L: E1.56 (IO43), U$1.DV1
DF_ENABLE: E1.94 (IO69), U$1.CA1
D_L: E1.70 (IO54), U$1.DK2
EMA0_L: E1.23 (IO16), U$1.AD2
EMA1_L: E1.22 (IO15), U$1.AE2
EMA2_L: E1.21 (IO14), U$1.AH2
F_L: E1.72 (IO56), U$1.DJ2
F_SET_L: E1.63 (IO49), U$1.DP2
GND: !TS.2, C1.2, C2.2, C3.2, C4.2, C33.-, C34.-, C35.-, E1.13 (GND), E1.27 (IO20), E1.28 (GND), E1.40 (GND), E1.45 (GND), E1.61 (GND), E1.76 (GND), E1.88 (GND), E1.97 (GND), E1.P$24 (GND), E1.P$26 (GND), E1.P$28 (GND), E1.P$30 (GND), SV2.2, SV2.10, U$1.AC2, U$1.AF1, U$1.AF2, U$1.AN1, U$1.AN2, U$1.AT1, U$1.AT2, U$1.BC1, U$1.BC2, U$1.BF1, U$1.BF2, U$1.BN1, U$1.BT1, U$1.CC1, U$1.CC2, U$1.CN1, U$1.DC1, U$1.DF1, U$1.DN1, U$1.DT1
IND1_L: E1.79 (IO61), U$1.CU2
IND2_L: E1.78 (IO60), U$1.CV2
INITIALIZE: E1.82 (IO64), U$1.CR1
INTERNAL_IO_L: E1.85 (IO66), U$1.CL1
INT_IN_PROGRESS_L: E1.2 (IO76), U$1.BP2
INT_RQST_L: E1.83 (IO65), U$1.CP1
IO_PAUSE_L: E1.92 (IN/GCLK2/OE2), U$1.CD1
IR00_L: E1.74 (IO58), U$1.DD2
IR01_L: E1.73 (IO57), U$1.DE2
KEY_CTL_L: E1.57 (IO44), U$1.DU2
LOAD_ADDR: E1.60 (IO47), U$1.DR2
LOAD_CNTL: E1.9 (IO5), U$1.BH2
MD00_L: E1.19 (IO13), U$1.AK1
MD01_L: E1.18 (IO12), U$1.AL1
MD02_L: E1.16 (IO11), U$1.AM1
MD03_L: E1.15 (IO10), U$1.AP1
MD04_L: E1.8 (IO4), U$1.BK1
MD05_L: E1.7 (IO3), U$1.BL1
MD06_L: E1.4 (IO2), U$1.BM1
MD07_L: E1.3 (IO/PD1), U$1.BP1
MD08_L: E1.71 (IO55), U$1.DK1
MD09_L: E1.69 (IO53), U$1.DL1
MD10_L: E1.67 (IO52), U$1.DM1
MD11_L: E1.65 (IO50), U$1.DP1
POWER_OK: E1.96 (IO71), U$1.BV2
RUN_L: E1.99 (IO73), U$1.BU2
SKIP_L: E1.81 (IO63), U$1.CS1
TCK2: E1.64 (TCK), SV2.1
TDI2: E1.6 (TDI), SV2.9
TDO2: E1.75 (TDO), SV2.3
TMS2: E1.17 (TMS), SV2.5
TP2: E1.91 (IN/GCLR), U$1.CE2
TP3: E1.89 (IN/GCLK1), U$1.CH2
TP4: E1.87 (IO/GCLK3), U$1.CJ2
TP_AA1: E1.25 (IO18), U$1.AA1
TP_AB1: E1.24 (IO17), U$1.AB1
TP_BA1: E1.11 (IO7), U$1.BA1
TP_BB1: E1.10 (IO6), U$1.BB1
TS1_L: E1.86 (IO67), U$1.CK2
TS_DISABLE_L: !TS.1, E1.54 (IO41)
USER_MODE_L: E1.66 (IO51), U$1.DM2
VCC: C33.+, C34.+, C35.+, SV2.4, U$1.AA2, U$1.BA2, U$1.CA2, VCCINT.1, VCCIO.1
VCCINT: C1.1, C3.1, E1.41 (VCCINT), E1.93 (VCCINT), E1.P$23 (VCCINT), E1.P$25 (VCCINT), VCCINT.2
VCCIO: C2.1, C4.1, E1.5 (VCCIO), E1.20 (VCCIO), E1.36 (VCCIO), E1.53 (VCCIO), E1.68 (VCCIO), E1.84 (VCCIO), E1.P$27 (VCCIO), E1.P$29 (VCCIO), E1.VCCIO@1 (VCCIO), E1.VCCIO@2 (VCCIO), VCCIO.2

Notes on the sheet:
E-CS-M8341-0-1
EAE Multiplexers and Timing Generator
